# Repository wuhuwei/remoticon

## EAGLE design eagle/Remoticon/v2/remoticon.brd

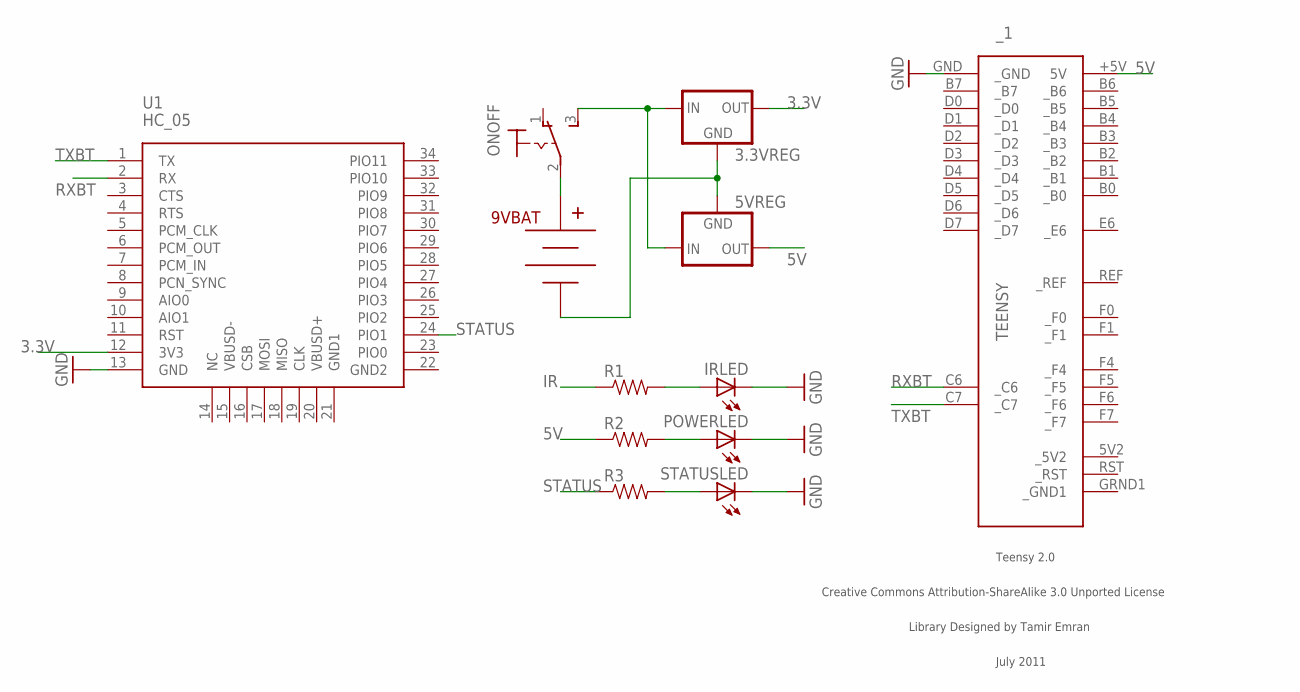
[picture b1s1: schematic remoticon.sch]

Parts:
3.3VREG: V_REG_LD1117VXX; 78XXL
5VREG: V_REG_78XX-TO-220; TO-220-ALT
9VBAT: BC9VPC
IRLED: LED5MM
ONOFF: 320-916
POWERLED: LED5MM
R1, R2, R3: RESISTOREZ; AXIAL-0.3EZ
STATUSLED: LED5MM
U1: HC_05; BLUETOOTH_SMD
_1: TEENSY

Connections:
3.3V: 3.3VREG.GND (OUT), U1.12 (3V3)
5V: 5VREG.OUT, R2.P$1 (1), _1.+5V (5V)
GND: IRLED.K (C), POWERLED.K (C), STATUSLED.K (C), U1.13 (GND), _1.GND (_GND)
IR: R1.P$1 (1)
unnamed: 9VBAT.V+, ONOFF.2
unnamed: 3.3VREG.OUT (IN), 5VREG.IN, ONOFF.3 (S)
unnamed: 3.3VREG.IN (GND), 5VREG.GND, 9VBAT.V-
unnamed: IRLED.A, R1.P$2 (2)
unnamed: POWERLED.A, R2.P$2 (2)
unnamed: R3.P$2 (2), STATUSLED.A
RXBT: U1.2 (RX), _1.C6 (_C6)
STATUS: R3.P$1 (1), U1.24 (PIO1)
TXBT: U1.1 (TX), _1.C7 (_C7)

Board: 2 copper layers, 12 parts (0 on the bottom side), 12 nets, no tracks yet.

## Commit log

2012-10-31 initial project commit
2012-11-02 started Rovi API integration
2012-11-04 displaying channels in a list
2012-11-08 Working scrolling guide
2012-11-09 added eagle schematic files, pcb layout is now waiting for cad layout to match with
2012-11-16 tv info loading, really gross messy code
2012-11-16 Fixed layout formatting
2012-11-19 adding in bluetooth connection gode, started setup process code
2012-11-19 more setup stuff
2012-11-20 finished setup page
2012-11-20 renaming some files
2012-11-21 menu button for connection
2012-11-21 menu button
2012-11-23 more remote code with buttons n stuff, ready to test
2012-11-23 adding loader to guide
2012-11-24 fixed merge problem - back button issues are still weird
2012-11-25 back behavior is not intuitive, but at least it is consistent now
2012-11-26 cleaning up repo, added loader for show info fetching, cleaned up guide UI
2012-11-26 adding numpad channel input w/ go button for selecting channel
2012-11-26 changing status buttons to be more bluetooth-y
2012-11-26 favorites done
2012-11-26 gitignore so i stop messing up the repo
2012-11-26 added interface to go to channel from any fragment
2012-11-27 adding remote codes for Peter's Toshiba
2012-11-28 prettifying favorites, adding favorites to other parts of app
2012-11-28 merge
2012-11-29 history working for favorites
2012-11-29 hacked up a back button workaround
2012-11-29 changed code sending protocol, it works
2012-11-29 adding res files
2012-11-30 some code refactoring, moving methods to menu activity
2012-12-01 mostly style changes, I think
2012-12-02 style changes, made guide tab more robust against internet disconnectivity
2012-12-02 code cleanup, changed margin to padding
2012-12-02 made guide disconnectivity messages in fragment instead of in a dialog, should be more robust now
2012-12-03 rotation disabled
2012-12-03 favorites button state UI tweaks
2012-12-03 changed remote buttons to be happy states

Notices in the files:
parts and their libraries:
teensy: Licensed Under Creative Commons
SparkFun-PowerIC: Licensing: CC v3.0 Share-Alike You are welcome to use this library for commercial purposes.
teensy: Creative Commons Attribution-ShareAlike 3.0 Unported License
